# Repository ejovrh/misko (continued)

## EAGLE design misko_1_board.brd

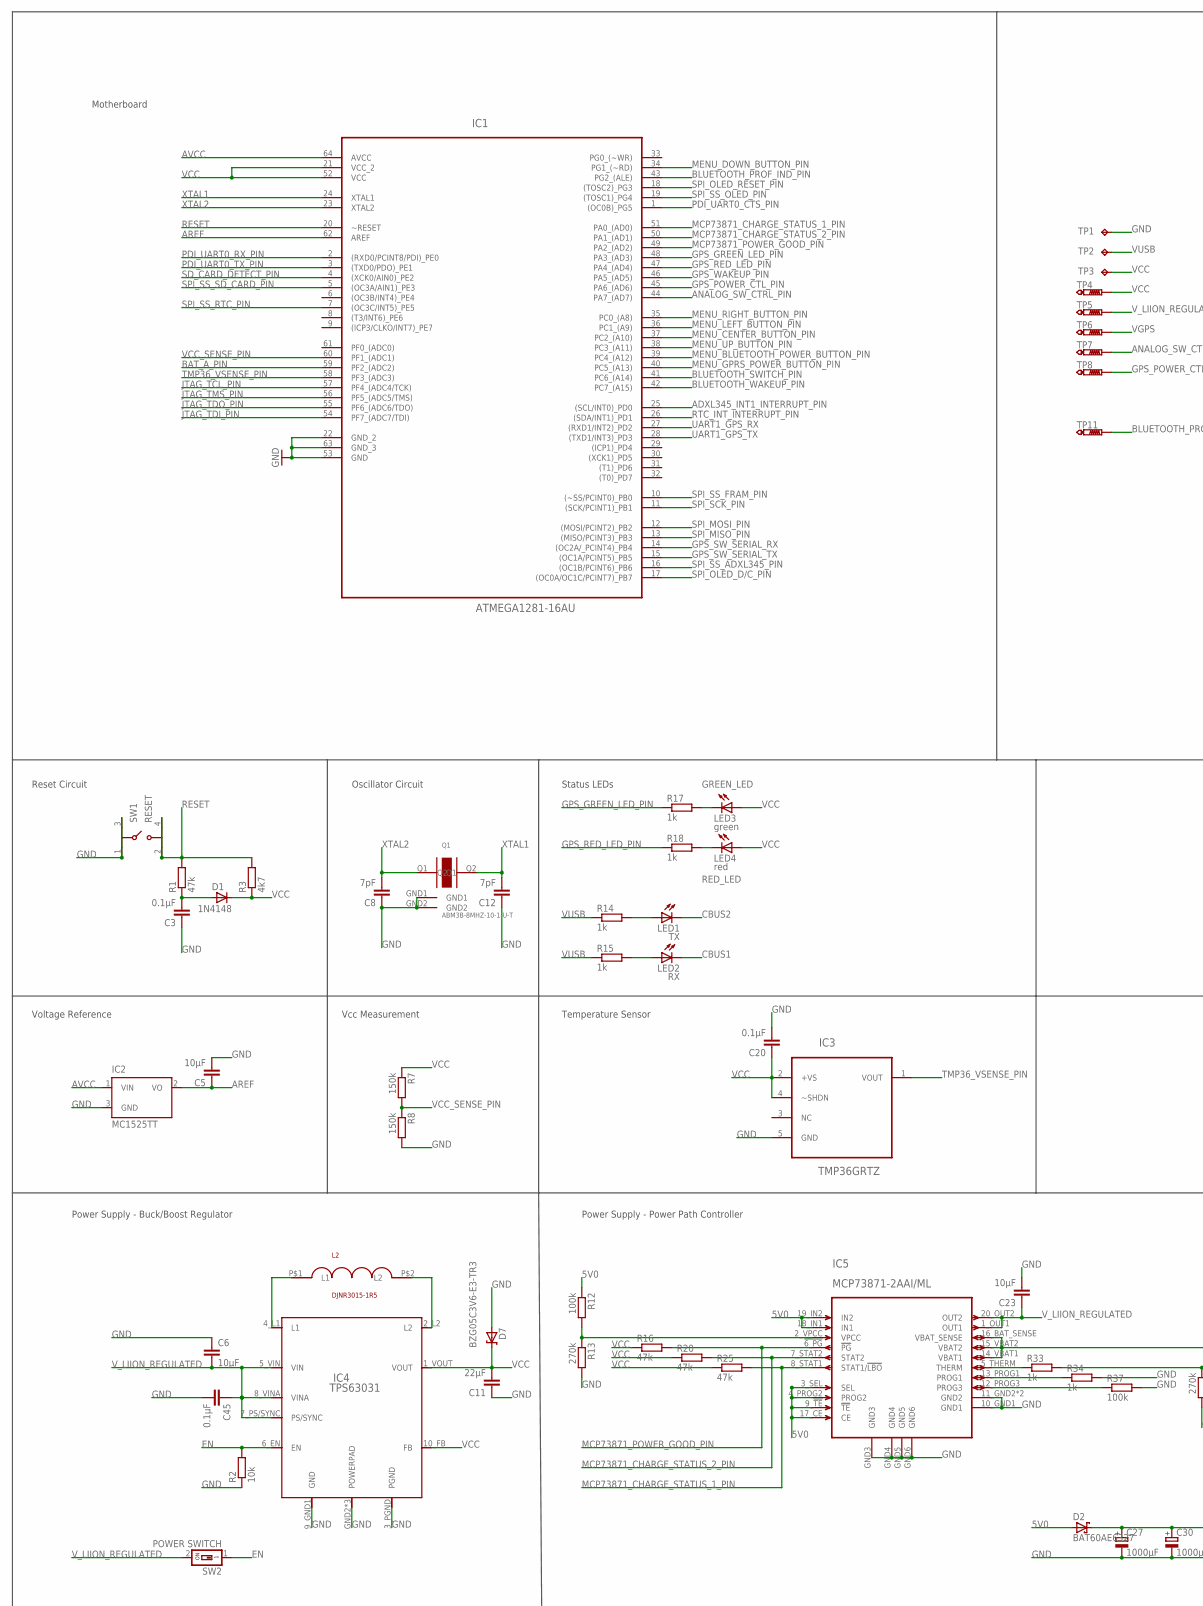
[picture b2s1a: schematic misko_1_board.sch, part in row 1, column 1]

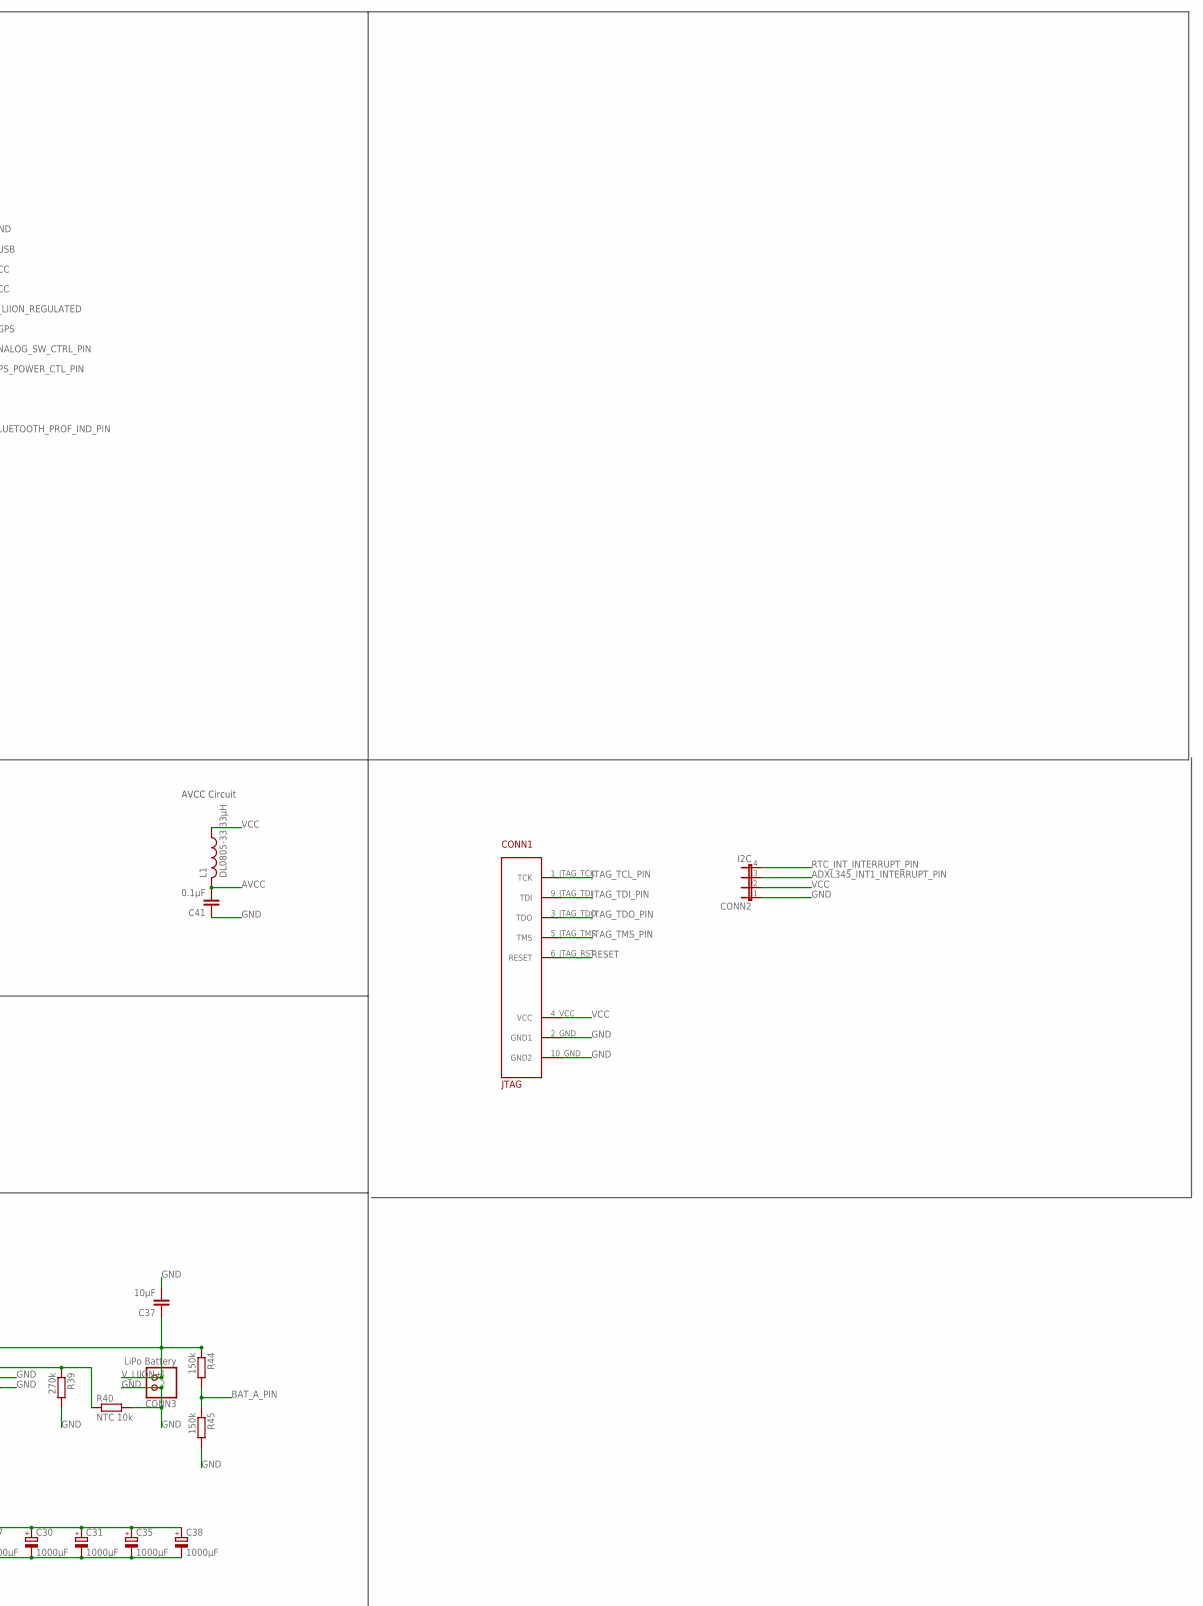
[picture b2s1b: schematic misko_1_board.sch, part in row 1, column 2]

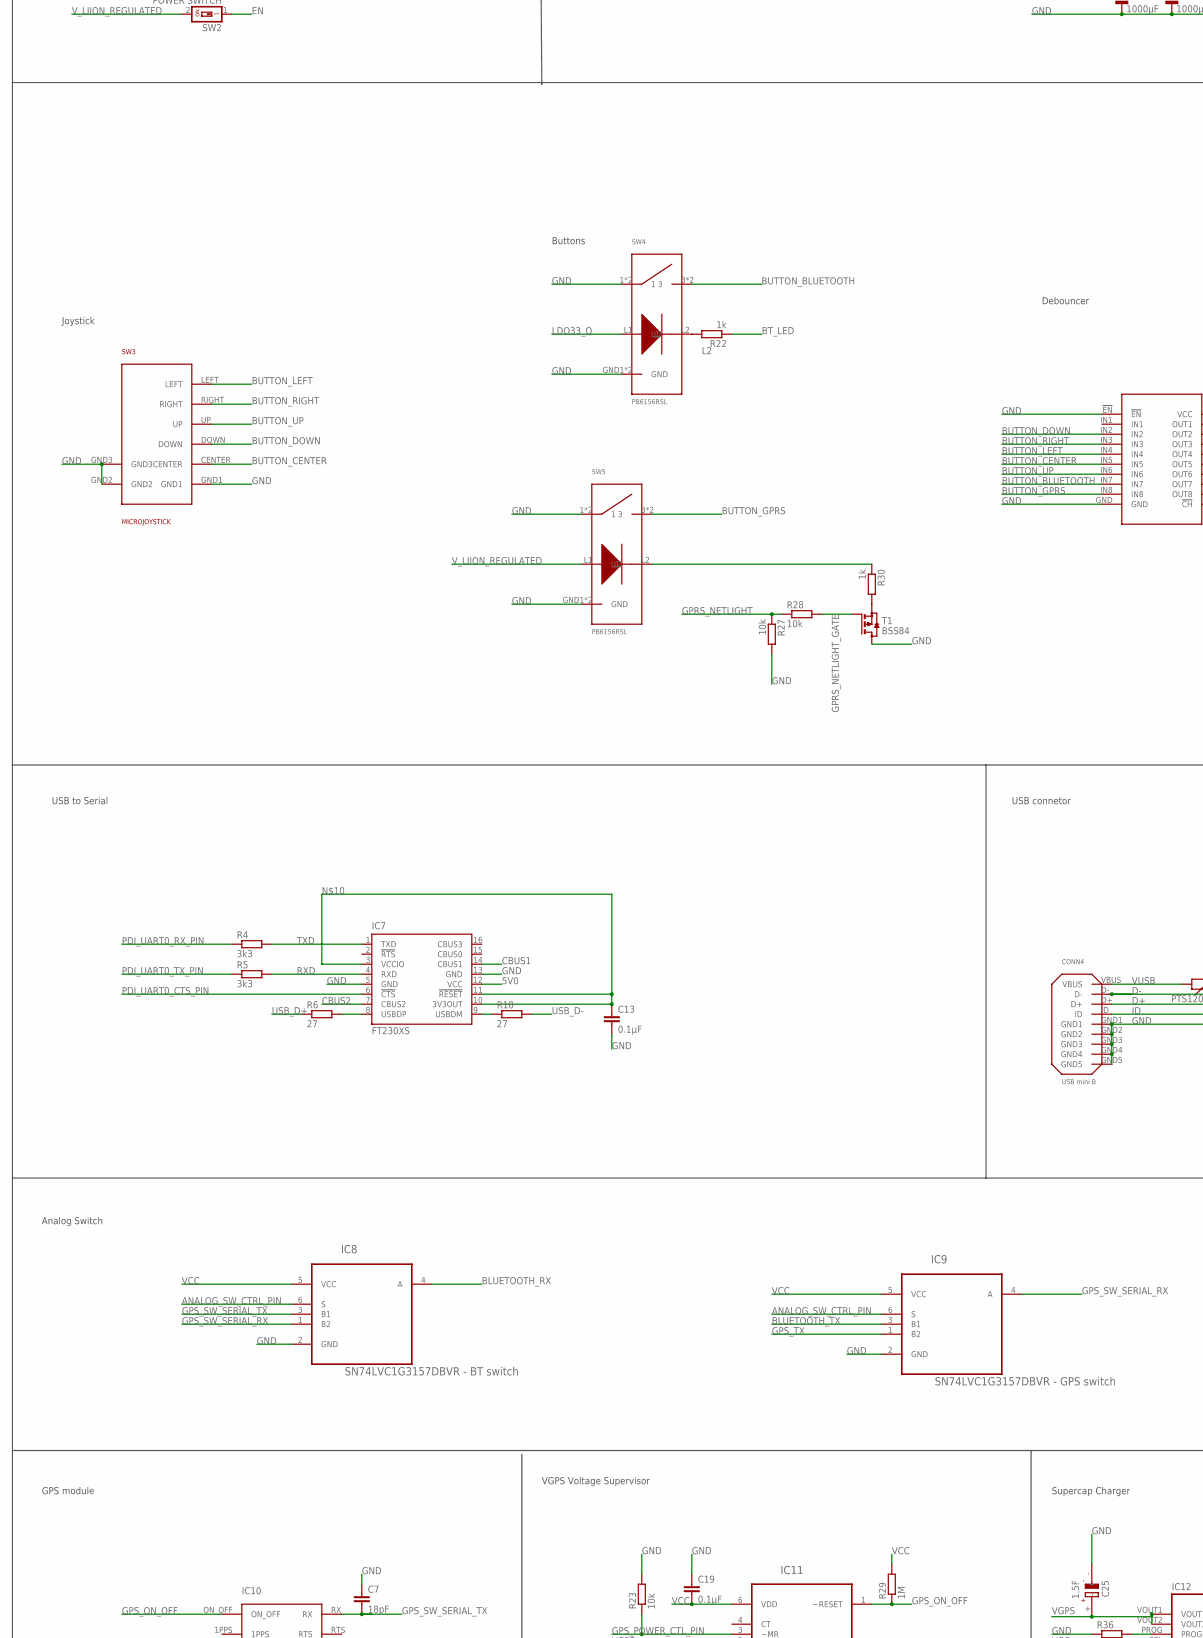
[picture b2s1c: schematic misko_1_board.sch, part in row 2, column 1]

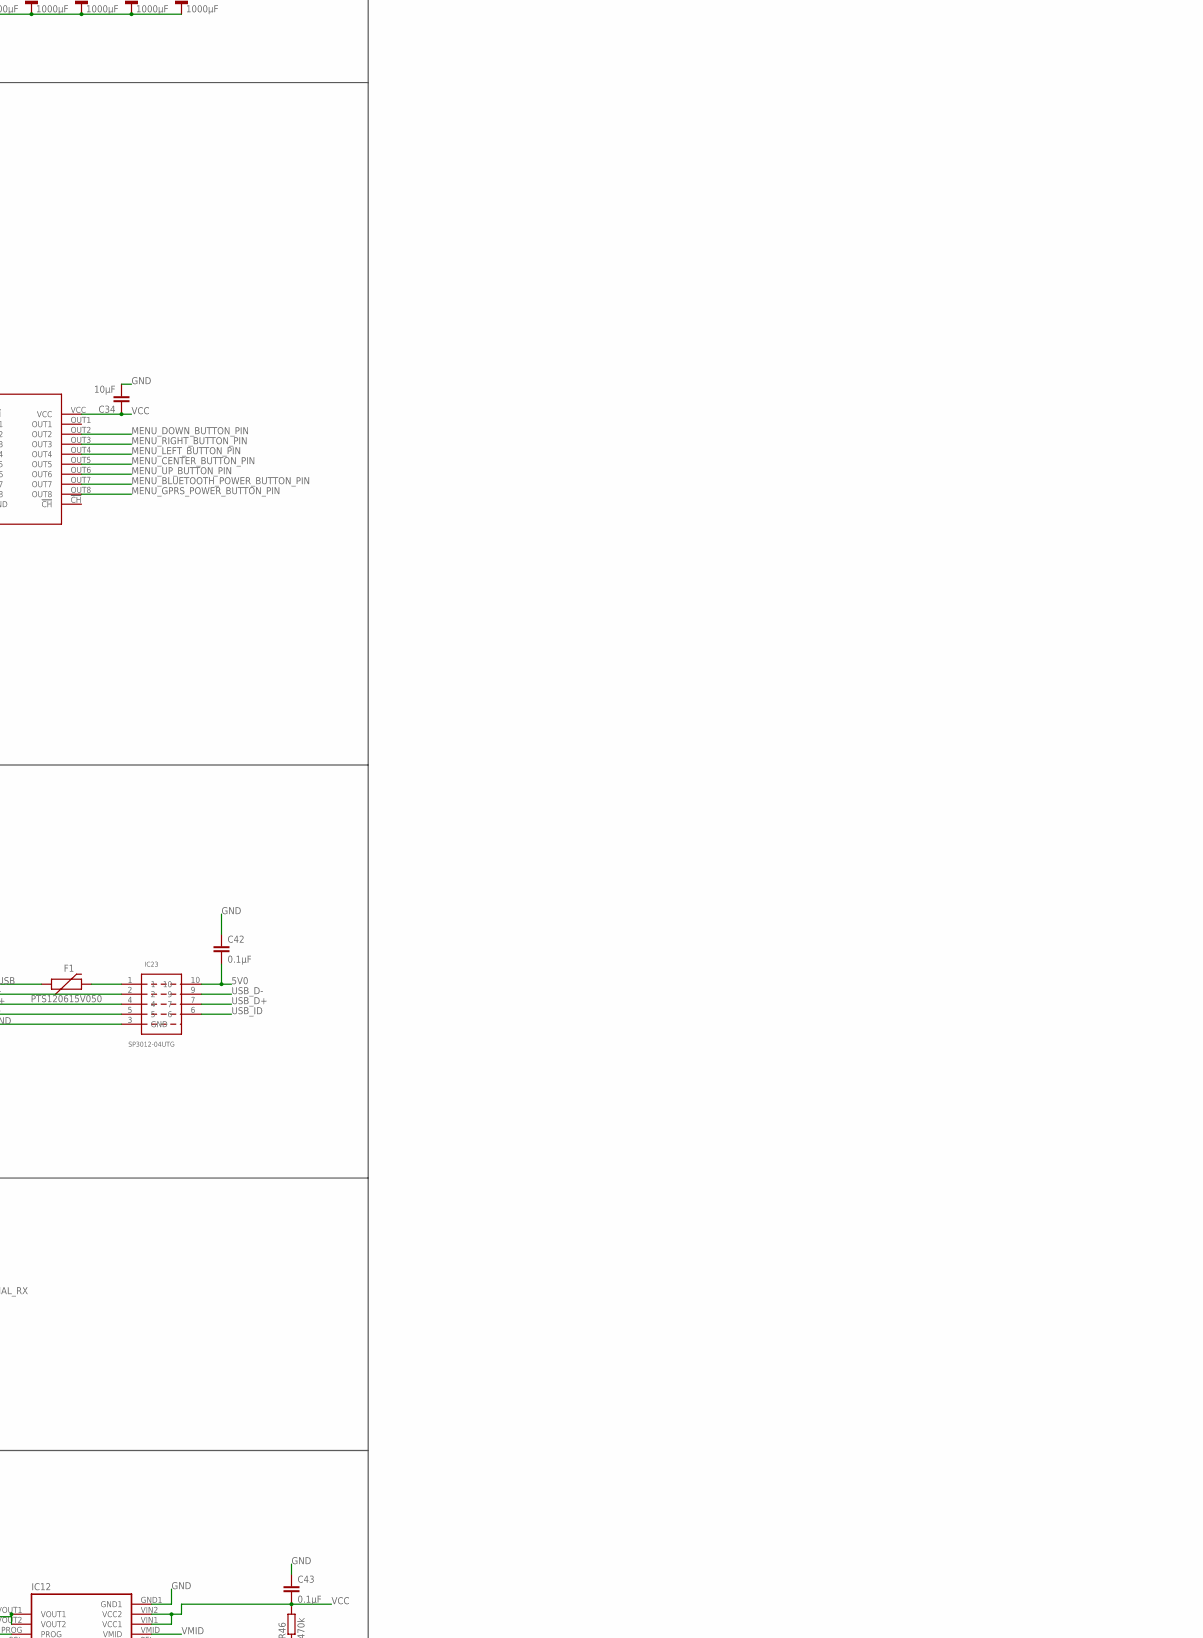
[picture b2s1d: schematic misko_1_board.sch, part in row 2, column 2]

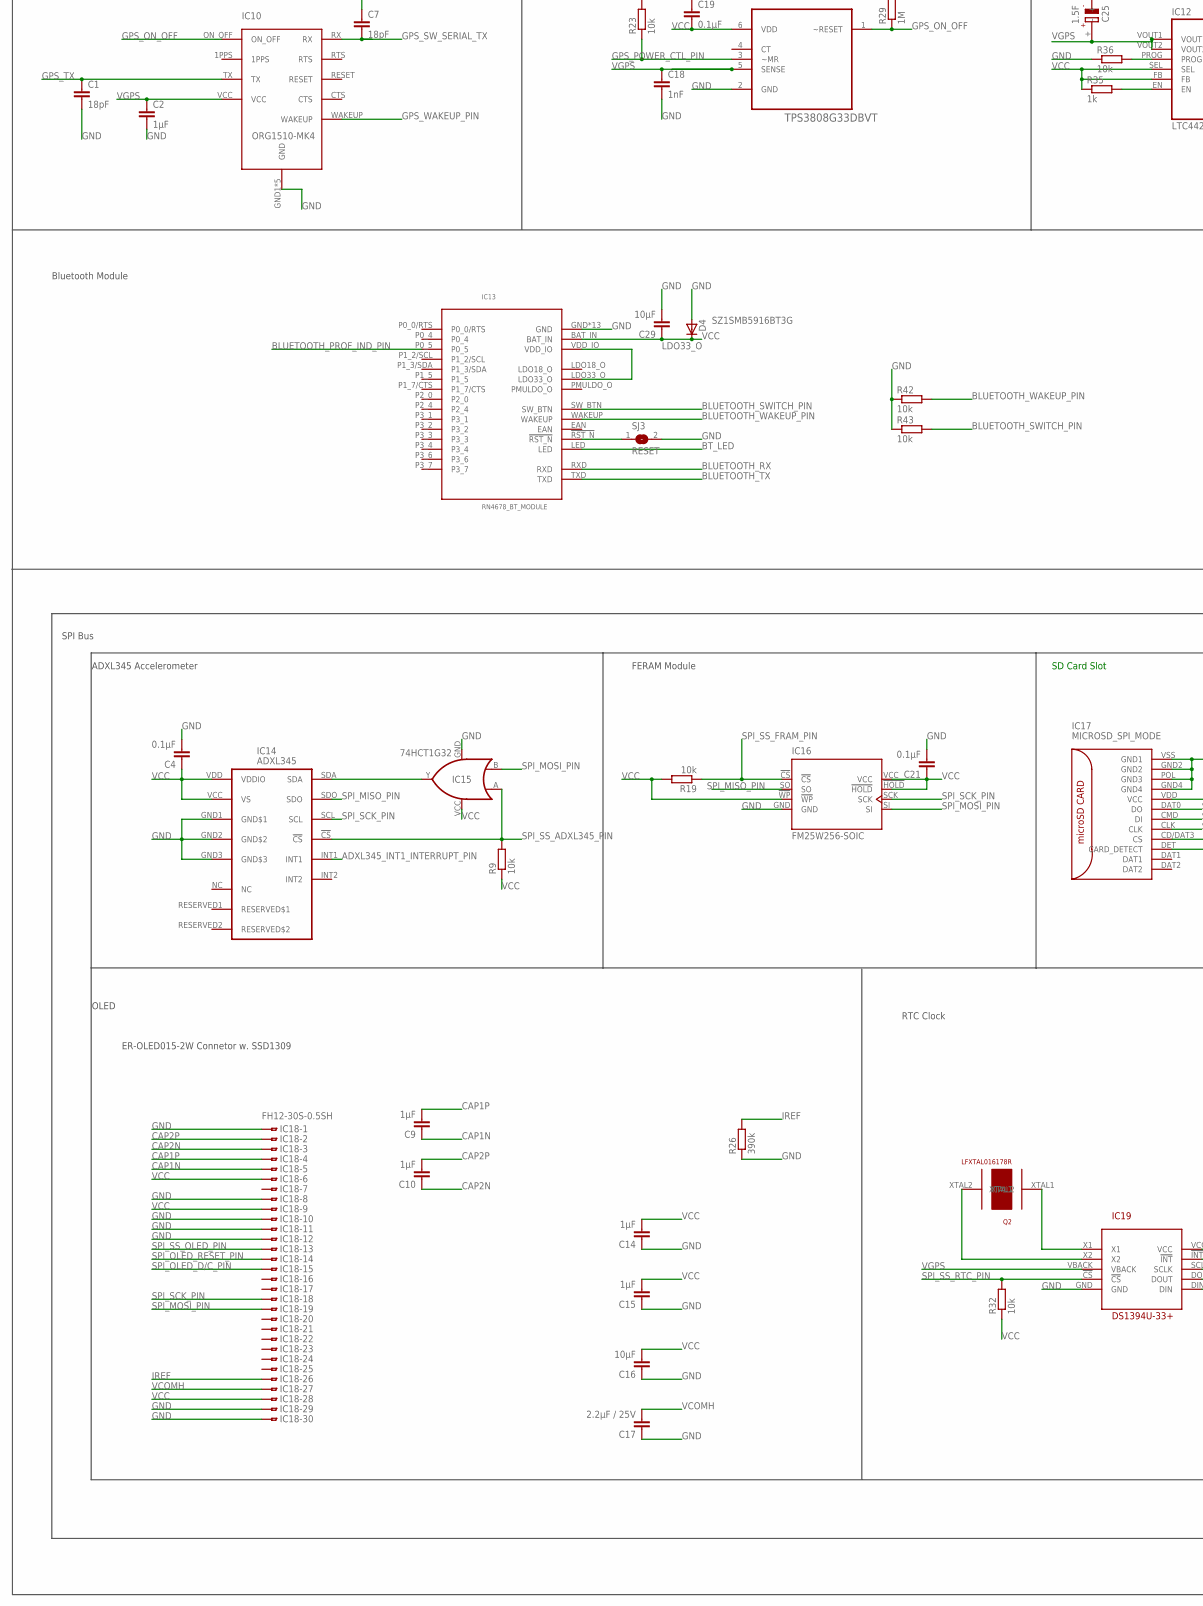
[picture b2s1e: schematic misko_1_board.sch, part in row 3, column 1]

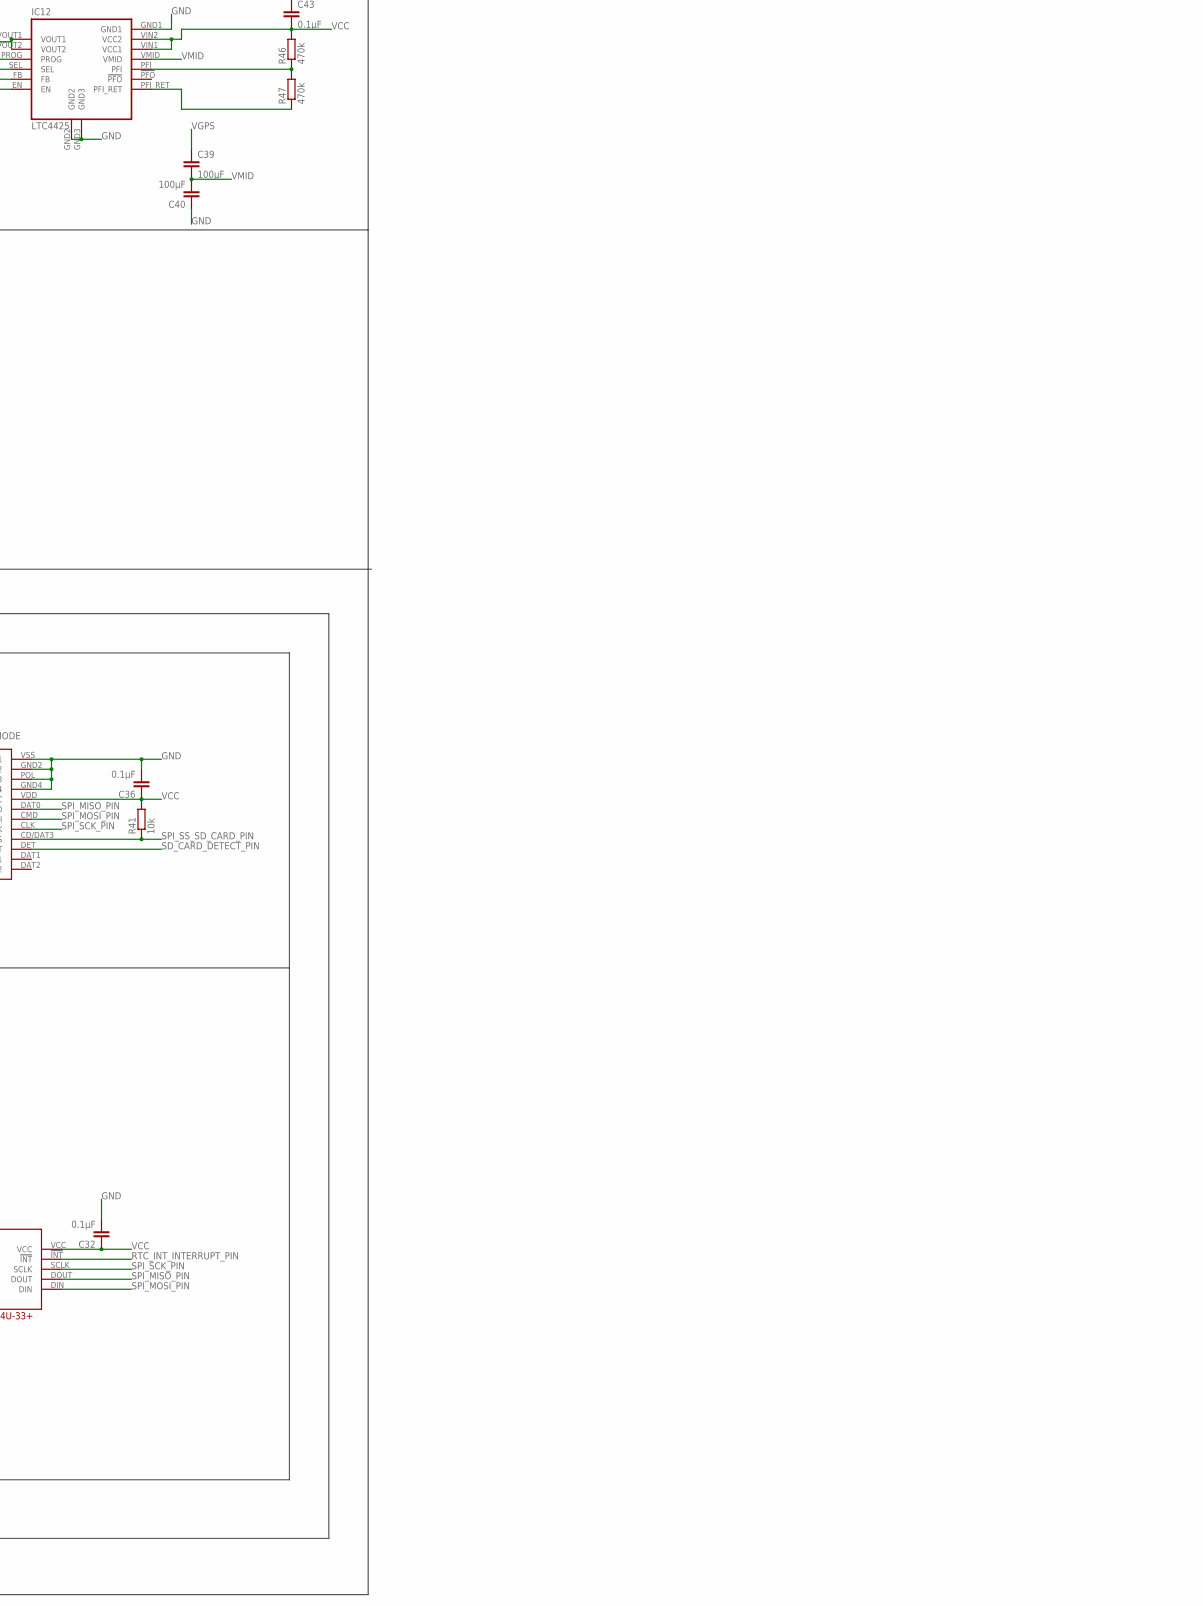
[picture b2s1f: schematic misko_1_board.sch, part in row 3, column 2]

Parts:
C1, C7: 18pF; C0805
C2, C9, C10, C14, C15: 1µF; C0805
C3, C4, C13, C19, C20, C21, C32, C36, C41, C42, C43, C45: 0.1µF; C0805
C5, C6, C16, C23, C29, C34, C37: 10µF; C0805
C8, C12: 7pF; C0805
C11: 22µF; C0805
C17: 2.2µF / 25V; C0805
C18: 1nF; C0805
C25: 1.5F; TH
C27, C30, C31, C35, C38: 1000µF; E5-10,5
C39, C40: 100µF; C0805
CONN1: JTAG; TH-JTAG
CONN2: I2C; JP4
CONN3: LiPo Battery; JST-PH-2-THM-RA
CONN4: USB mini B; SMT
D1: 1N4148; D0805
D2: BAT60AE6327; SOD323_ST
D4: SZ1SMB5916BT3G; SMB
D7: BZG05C3V6-E3-TR3; DO-214
F1: PTS120615V050; 1206
IC1: ATMEGA1281-16AU; QFP80P1600X1600X120-64N
IC2: MC1525TT; SOT23
IC3: TMP36GRTZ; SOT95P280X145-5N
IC4: TPS63031; SMT
IC5: MCP73871-2AAI/ML; QFN50P400X400X100-21N
IC6: MAX6818; TSSOP20
IC7: FT230XS; SSOP16
IC8: SN74LVC1G3157DBVR - BT switch; SOT95P280X145-6N
IC9: SN74LVC1G3157DBVR - GPS switch; SOT95P280X145-6N
IC10: ORG1510-MK4; PACKAGE
IC11: TPS3808G33DBVT; SOT95P280X145-6N
IC12: LTC4425; MSOP
IC13: RN4678_BT_MODULE; SMT
IC14: ADXL345; LGA14
IC15: 74HCT1G32; SOT353/5
IC16: FM25W256-SOIC; SOIC08
IC17: MICROSD_SPI_MODE; MICRO_SD_CONNECTOR
IC18: FH12-30S-0.5SH
IC19: DS1394U-33+; 10UMAX
IC23: SP3012-04UTG; μDFN-10
L1: DL0805-33 33µH; L0805
L2: DJNR3015-1R5; FFF
LED1: TX; CHIPLED_1206
LED2: RX; CHIPLED_1206
LED3: green; LED2X5
LED4: red; LED2X5
Q1: ABM3B-8MHZ-10-1-U-T; SMT
Q2: LFXTAL016178R; SMD
R1, R16, R20, R25: 47k; R0805
R2, R9, R19, R23, R27, R28, R32, R36, R41, R42, R43: 10k; R0805
R3: 4k7; R0805
R4, R5: 3k3; R0805
R6, R10: 27; R0805
R7, R8, R44, R45: 150k; R0805
R12, R37: 100k; R0805
R13, R39: 270k; R0805
R14, R15, R17, R18, R22, R30, R33, R34, R35: 1k; R0805
R26: 390k; R0805
R29: 1M; R0805
R40: NTC 10k; 0204/5
R46, R47: 470k; R0805
SJ3: RESET; SJW
SW1: RESET; 430152050836
SW2: POWER SWITCH; SMS-001
SW3: MICROJOYSTICK
SW4, SW5: PB6156RSL; TH
T1: BSS84; SOT23
TP1, TP2, TP3: GND; P1-17Y
TP4: VCC; TP14R
TP5: VLiIon Regulated; TP14R
TP6: VGPS; TP14R
TP7: Analogue Switch CRTL Pin; TP14R
TP8: GPS Power CTRL Pin; B1,27
TP11: Bluetooth Wakeup Pin; TP14R

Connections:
5V0: C42.2, D2.A, IC5.3_SEL (SEL), IC5.4_PROG2 (PROG2), IC5.9_!TE! (!TE!), IC5.17_CE (CE), IC5.18_IN1 (IN1), IC5.19_IN2 (IN2), IC7.12 (VCC), IC23.10, R12.1
ADXL345SDA: IC14.SDA, IC15.Y
ADXL345_INT1_INTERRUPT_PIN: CONN2.3, IC1.25 ((SCL/INT0)_PD0), IC14.INT1
ANALOG_SW_CTRL_PIN: IC1.44 (PA7_(AD7)), IC8.6 (S), IC9.6 (S), TP7.TP
AREF: C5.1, IC1.62 (AREF), IC2.2 (VO)
AVCC: C41.2, IC1.64 (AVCC), IC2.1 (VIN), L1.2
BAT_A_PIN: IC1.59 (PF2_(ADC2)), R44.2, R45.1
BLUETOOTH_PROF_IND_PIN: IC1.43 (PG2_(ALE)), IC13.P0_5, TP11.TP
BLUETOOTH_RX: IC8.4 (A), IC13.RXD
BLUETOOTH_SWITCH_PIN: IC1.41 (PC6_(A14)), IC13.SW_BTN, R43.2
BLUETOOTH_TX: IC9.3 (B1), IC13.TXD
BLUETOOTH_WAKEUP_PIN: IC1.42 (PC7_(A15)), IC13.WAKEUP, R42.2
BT_LED: IC13.LED, R22.1
BUTTON_BLUETOOTH: IC6.IN7, SW4.3, SW4.4 (3)
BUTTON_CENTER: IC6.IN5, SW3.CENTER
BUTTON_DOWN: IC6.IN2, SW3.DOWN
BUTTON_GPRS: IC6.IN8, SW5.3, SW5.4 (3)
BUTTON_LEFT: IC6.IN4, SW3.LEFT
BUTTON_RIGHT: IC6.IN3, SW3.RIGHT
BUTTON_UP: IC6.IN6, SW3.UP
CAP1N: C9.1, IC18.5
CAP1P: C9.2, IC18.4
CAP2N: C10.1, IC18.3
CAP2P: C10.2, IC18.2
CBUS1: IC7.14 (CBUS1), LED2.C
CBUS2: IC7.7 (CBUS2), LED1.C
D+: CONN4.D+, IC23.4
D-: CONN4.D-, IC23.2
EN: IC4.6_EN (EN), R2.2, SW2.1
GND: C1.2, C2.2, C3.1, C4.2, C5.2, C6.1, C7.1, C8.1, C11.1, C12.1, C13.2, C14.1, C15.1, C16.1, C17.1, C18.2, C19.1, C20.2, C21.2, C23.2, C25.-, C27.-, C29.2, C30.-, C31.-, C32.2, C34.2, C35.-, C36.2, C37.2, C38.-, C40.1, C41.1, C42.1, C43.1, C45.2, CONN1.2_GND (GND1), CONN1.10_GND (GND2), CONN2.1, CONN3.2 (1), CONN4.GND1, CONN4.GND2, CONN4.GND3, CONN4.GND4, CONN4.GND5, D4.A, D7.AN, IC1.22 (GND_2), IC1.53 (GND), IC1.63 (GND_3), IC2.3 (GND), IC3.5 (GND), IC4.3_PGND (PGND), IC4.9_GND1 (GND), IC4.GND2 (POWERPAD), IC4.GND3 (POWERPAD), IC4.GND4 (POWERPAD), IC5.10_GND1 (GND1), IC5.11_GND2 (GND2), IC5.GND2, IC5.GND3, IC5.GND4, IC5.GND5, IC5.GND6, IC6.!EN!, IC6.GND, IC7.5 (GND), IC7.13 (GND), IC8.2 (GND), IC9.2 (GND), IC10.GND1 (GND), IC10.GND2 (GND), IC10.GND3 (GND), IC10.GND4 (GND), IC10.GND5 (GND), IC11.2 (GND), IC12.GND1, IC12.GND2, IC12.GND3, IC13.GND, IC13.GND1 (GND), IC13.GND2 (GND), IC13.GND3 (GND), IC13.GND4 (GND), IC13.GND5 (GND), IC13.GND6 (GND), IC13.GND7 (GND), IC13.GND8 (GND), IC13.GND9 (GND), IC13.GND10 (GND), IC13.GND11 (GND), IC13.GND12 (GND), IC14.GND1 (GND$1), IC14.GND2 (GND$2), IC14.GND3 (GND$3), IC15.GND, IC16.GND, IC17.GND2, IC17.GND4, IC17.POL (GND3), IC17.VSS (GND1), IC18.1, IC18.8, IC18.10, IC18.11, IC18.12, IC18.29, IC18.30, IC19.GND, IC23.3 (GND), Q1.GND1, Q1.GND2, R2.1, R8.2, R13.2, R23.2, R26.1, R27.2, R34.2, R36.1, R37.2, R39.2, R40.2, R42.1, R43.1, R45.2, SJ3.2, SW1.1, SW1.3, SW3.GND1, SW3.GND2, SW3.GND3, SW4.1, SW4.2 (1), SW4.GND1 (GND), SW4.GND2 (GND), SW5.1, SW5.2 (1), SW5.GND1 (GND), SW5.GND2 (GND), T1.3 (D), TP1.TP
GPRS_NETLIGHT: R27.1, R28.1
GPRS_NETLIGHT_GATE: R28.2, T1.1 (G)
GPS_GREEN_LED_PIN: IC1.48 (PA3_(AD3)), R17.1
GPS_ON_OFF: IC10.ON_OFF, IC11.1 (~RESET), R29.1
GPS_POWER_CTL_PIN: IC1.45 (PA6_(AD6)), IC11.3 (~MR), R23.1, TP8.TP
GPS_RED_LED_PIN: IC1.47 (PA4_(AD4)), R18.1
GPS_SW_SERIAL_RX: IC1.14 ((OC2A/_PCINT4)_PB4), IC8.1 (B2), IC9.4 (A)
GPS_SW_SERIAL_TX: C7.2, IC1.15 ((OC1A/PCINT5)_PB5), IC8.3 (B1), IC10.RX
GPS_TX: C1.1, IC9.1 (B2), IC10.TX
GPS_WAKEUP_PIN: IC1.46 (PA5_(AD5)), IC10.WAKEUP
GREEN_LED: LED3.K (C), R17.2
ID: CONN4.ID, IC23.5
IREF: IC18.26, R26.2
JTAG_TCL_PIN: CONN1.1_JTAG_TCK (TCK), IC1.57 (PF4_(ADC4/TCK))
JTAG_TDI_PIN: CONN1.9_JTAG_TDI (TDI), IC1.54 (PF7_(ADC7/TDI))
JTAG_TDO_PIN: CONN1.3_JTAG_TDO (TDO), IC1.55 (PF6_(ADC6/TDO))
JTAG_TMS_PIN: CONN1.5_JTAG_TMS (TMS), IC1.56 (PF5_(ADC5/TMS))
L2: R22.2, SW4.L2
LDO18_O: IC13.LDO18_O
LDO33_O: IC13.LDO33_O, IC13.VDD_IO, SW4.L1
LTC4425_EN: IC12.EN, R35.2
LTC4425_PROG: IC12.PROG, R36.2
L_L1: IC4.4_L1 (L1), L2.P$1 (L1)
L_L2: IC4.2_L2 (L2), L2.P$2 (L2)
MCP73871_CHARGE_STATUS_1_PIN: IC1.51 (PA0_(AD0)), IC5.8_STAT1 (STAT1/!LBO!), R25.2
MCP73871_CHARGE_STATUS_2_PIN: IC1.50 (PA1_(AD1)), IC5.7_STAT2 (STAT2), R20.2
MCP73871_POWER_GOOD_PIN: IC1.49 (PA2_(AD2)), IC5.!6_PG! (!PG!), R16.2
MENU_BLUETOOTH_POWER_BUTTON_PIN: IC1.39 (PC4_(A12)), IC6.OUT7
MENU_CENTER_BUTTON_PIN: IC1.37 (PC2_(A10)), IC6.OUT5
MENU_DOWN_BUTTON_PIN: IC1.34 (PG1_(~RD)), IC6.OUT2
MENU_GPRS_POWER_BUTTON_PIN: IC1.40 (PC5_(A13)), IC6.OUT8
MENU_LEFT_BUTTON_PIN: IC1.36 (PC1_(A9)), IC6.OUT4
MENU_RIGHT_BUTTON_PIN: IC1.35 (PC0_(A8)), IC6.OUT3
MENU_UP_BUTTON_PIN: IC1.38 (PC3_(A11)), IC6.OUT6
unnamed: R30.1, SW5.L2
unnamed: R30.2, T1.2 (S)
unnamed: F1.2, IC23.1
unnamed: C27.+, C30.+, C31.+, C35.+, C38.+, D2.C
unnamed: C13.1, IC7.3 (VCCIO), IC7.10 (3V3OUT), IC7.11 (!RESET)
unnamed: IC13.!RST_N!, SJ3.1
unnamed: R33.2, R39.1, R40.1
unnamed: C3.2, D1.A, R1.1
PDI_UART0_CTS_PIN: IC1.1 ((OC0B)_PG5), IC7.6 (!CTS)
PDI_UART0_RX_PIN: IC1.2 ((RXD0/PCINT8/PDI)_PE0), R4.1
PDI_UART0_TX_PIN: IC1.3 ((TXD0/PDO)_PE1), R5.1
PFI: IC12.PFI, R46.1, R47.2
PFI_RET: IC12.PFI_RET, R47.1
PROG1: IC5.13_PROG1 (PROG1), R34.1
PROG3: IC5.12_PROG3 (PROG3), R37.1
RED_LED: LED4.K (C), R18.2
RESET: CONN1.6_JTAG_RST (RESET), IC1.20 (~RESET), R1.2, R3.2, SW1.2, SW1.4
RTC_INT_INTERRUPT_PIN: CONN2.4, IC1.26 ((SDA/INT1)_PD1), IC19.!INT!
RTC_XTAL1: IC19.X1, Q2.XTAL1
RTC_XTAL2: IC19.X2, Q2.XTAL2
RXD: IC7.4 (RXD), R5.2
SD_CARD_DETECT_PIN: IC1.4 ((XCK0/AIN0)_PE2), IC17.DET (CARD_DETECT)
SPI_MISO_PIN: IC1.13 ((MISO/PCINT3)_PB3), IC14.SDO, IC16.SO, IC17.DAT0 (DO), IC19.DOUT
SPI_MOSI_PIN: IC1.12 ((MOSI/PCINT2)_PB2), IC15.B, IC16.SI, IC17.CMD (DI), IC18.19, IC19.DIN
SPI_OLED_D/C_PIN: IC1.17 ((OC0A/OC1C/PCINT7)_PB7), IC18.15
SPI_OLED_RESET_PIN: IC1.18 ((TOSC2)_PG3), IC18.14
SPI_SCK_PIN: IC1.11 ((SCK/PCINT1)_PB1), IC14.SCL, IC16.SCK, IC17.CLK, IC18.18, IC19.SCLK
SPI_SS_ADXL345_PIN: IC1.16 ((OC1B/PCINT6)_PB6), IC14.!CS!, IC15.A, R9.2
SPI_SS_FRAM_PIN: IC1.10 ((~SS/PCINT0)_PB0), IC16.!CS!, R19.1
SPI_SS_OLED_PIN: IC1.19 ((TOSC1)_PG4), IC18.13
SPI_SS_RTC_PIN: IC1.7 ((OC3C/INT5)_PE5), IC19.!CS!, R32.2
SPI_SS_SD_CARD_PIN: IC1.5 ((OC3A/AIN1)_PE3), IC17.CD/DAT3 (CS), R41.1
THERM: IC5.5_THERM (THERM), R33.1
TMP36_VSENSE_PIN: IC1.58 (PF3_(ADC3)), IC3.1 (VOUT)
TXD: IC7.1 (TXD), R4.2
UART1_GPS_RX: IC1.27 ((RXD1/INT2)_PD2)
UART1_GPS_TX: IC1.28 ((TXD1/INT3)_PD3)
USBDM: IC7.9 (USBDM), R10.1
USBDP: IC7.8 (USBDP), R6.2
USB_D+: IC23.7, R6.1
USB_D-: IC23.9, R10.2
USB_ID: IC23.6
USB_RX_LED: LED1.A, R14.2
USB_TX_LED: LED2.A, R15.2
VCC: C4.1, C11.2, C14.2, C15.2, C16.2, C19.2, C20.1, C21.1, C29.1, C32.1, C34.1, C36.1, C43.2, CONN1.4_VCC (VCC), CONN2.2, D1.C, D4.C, D7.CAT, IC1.21 (VCC_2), IC1.52 (VCC), IC3.2 (+VS), IC3.4 (~SHDN), IC4.1_VOUT (VOUT), IC4.10_FB (FB), IC6.VCC, IC8.5 (VCC), IC9.5 (VCC), IC11.6 (VDD), IC12.FB, IC12.SEL, IC12.VIN1 (VCC1), IC12.VIN2 (VCC2), IC13.BAT_IN, IC14.VCC (VS), IC14.VDD (VDDIO), IC15.VCC, IC16.!HOLD!, IC16.!WP!, IC16.VCC, IC17.VDD (VCC), IC18.6, IC18.9, IC18.28, IC19.VCC, L1.1, LED3.A, LED4.A, R3.1, R7.1, R9.1, R16.1, R19.2, R20.1, R25.1, R29.2, R32.1, R35.1, R41.2, R46.2, TP3.TP, TP4.TP
VCC_SENSE_PIN: IC1.60 (PF1_(ADC1)), R7.2, R8.1
VCOMH: C17.2, IC18.27
VGPS: C2.1, C18.1, C25.+, C39.1, IC10.VCC, IC11.5 (SENSE), IC12.VOUT1, IC12.VOUT2, IC19.VBACK, TP6.TP
VMID: C39.2, C40.2, IC12.VMID
VPCC: IC5.2_VPCC (VPCC), R12.2, R13.1
VUSB: CONN4.VBUS, F1.1, R14.1, R15.1, TP2.TP
V_LIION+: C37.1, CONN3.1 (2), IC5.14_VBAT1 (VBAT1), IC5.15_VBAT2 (VBAT2), IC5.16_BAT_SENSE (VBAT_SENSE), R44.1
V_LIION_REGULATED: C6.2, C23.1, C45.1, IC4.5_VIN (VIN), IC4.7_PS/SYNC (PS/SYNC), IC4.8_VINA (VINA), IC5.1_OUT1 (OUT1), IC5.20_OUT2 (OUT2), SW2.2, SW5.L1, TP5.TP
XTAL1: C12.2, IC1.24 (XTAL1), Q1.Q2
XTAL2: C8.2, IC1.23 (XTAL2), Q1.Q1

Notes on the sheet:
Joystick
Temperature Sensor
Analog Switch
Motherboard
Voltage Reference
Vcc Measurement
Power Supply - Buck/Boost Regulator
Power Supply - Power Path Controller
USB to Serial
GPS module
Supercap Charger
Bluetooth Module
SPI Bus
ADXL345 Accelerometer
FERAM Module
Status LEDs
Reset Circuit
Oscillator Circuit
AVCC Circuit
SD Card Slot
OLED
ER-OLED015-2W Connetor w. SSD1309
RTC Clock
Buttons
Debouncer
USB connetor
VGPS Voltage Supervisor

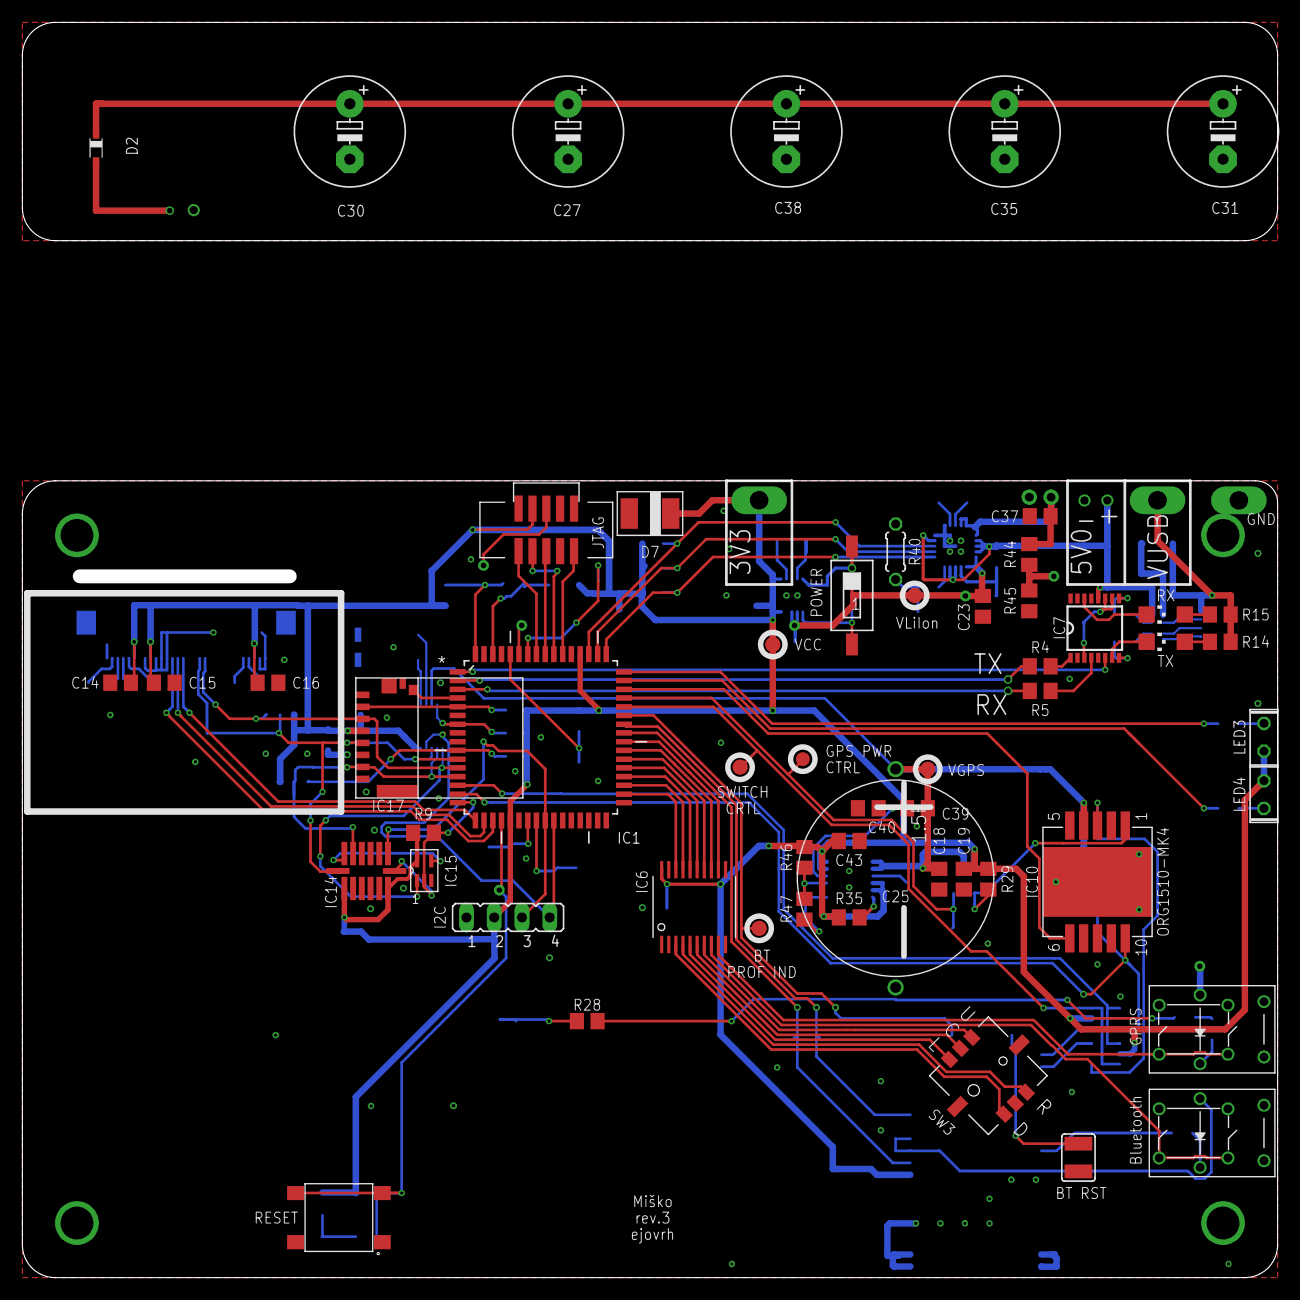
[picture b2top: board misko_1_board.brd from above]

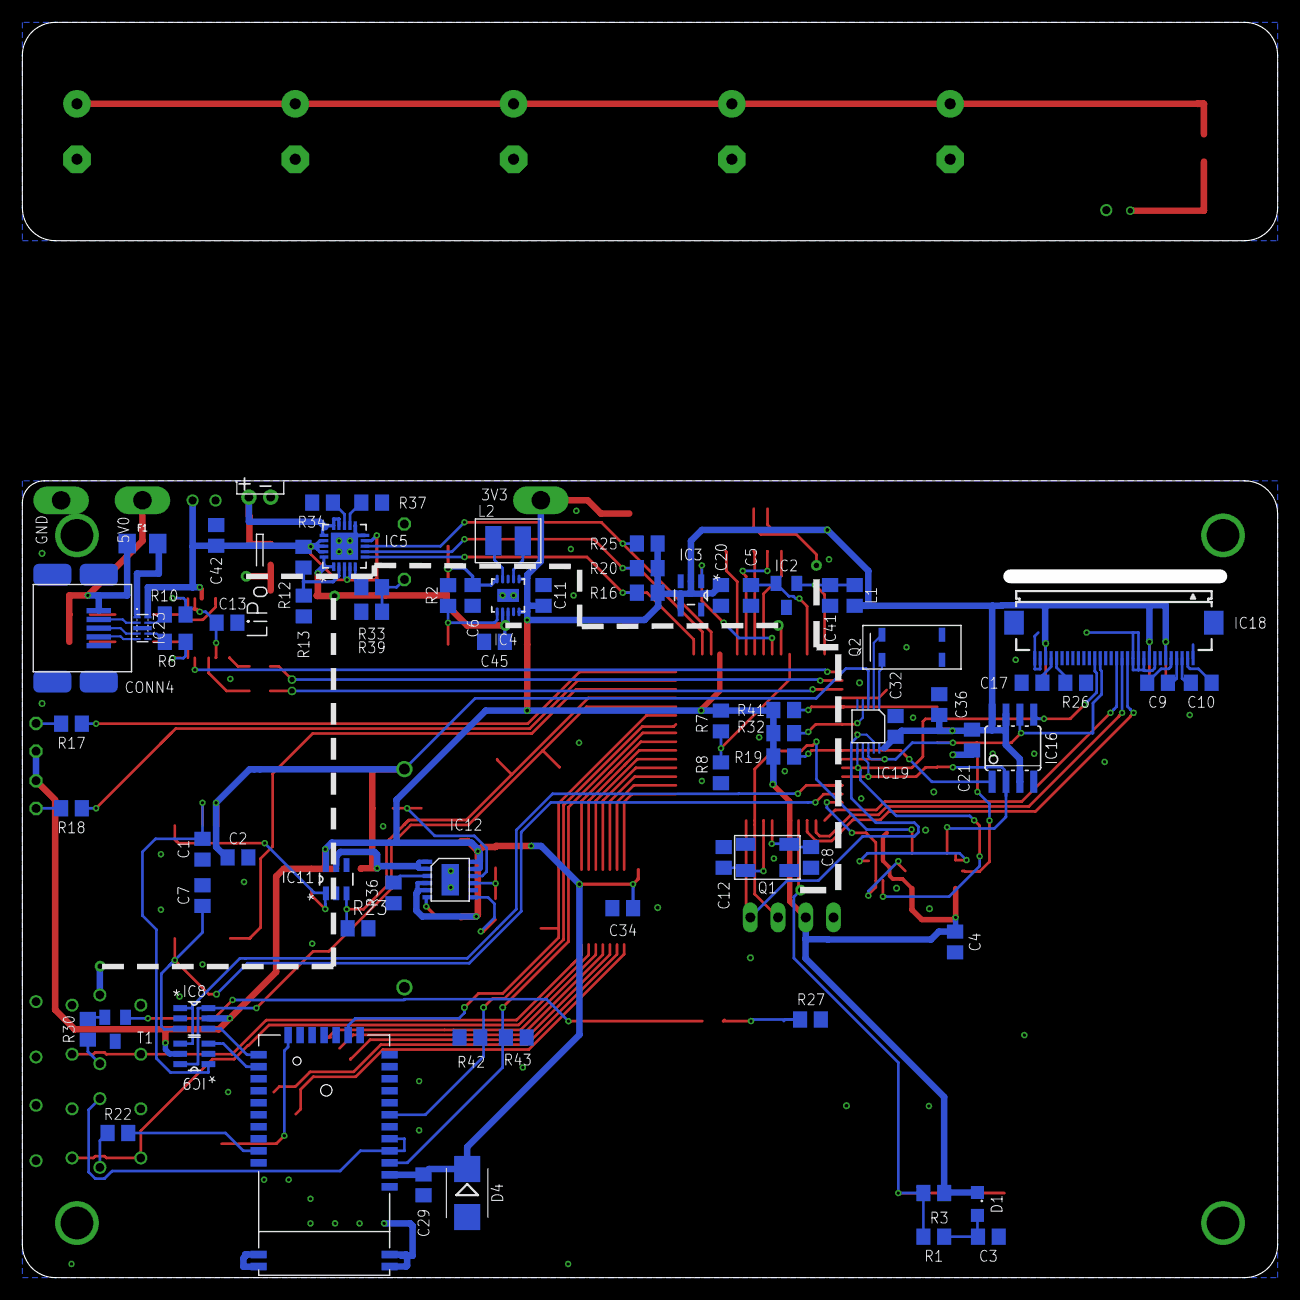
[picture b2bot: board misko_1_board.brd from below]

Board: 2 copper layers, 115.0 x 73.0 mm, 134 parts (75 on the bottom side), 115 nets.
